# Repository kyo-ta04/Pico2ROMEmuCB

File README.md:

# Pico2ROMEmu - RP2350B Core Board Version
<!--  -->

このプロジェクトは Pico2ROMEmuに RP2350B Core Boardを使用した簡単で高速なROMエミュレータです  
[English Readme](./README.en.md)

## 特徴
- 詳しくは[Pico2ROMEmu](https://github.com/kyo-ta04/Pico2ROMEmuBR)をご覧ください。

## 構成
- KiCad 回路図、PCB、ガーバーファイルはこちら→ [./PCB/](./PCB/) (**2025/11/09 追加 V1.0 R0.1**)
  - KiCad Ver9.0.6、 JLCPCB Fabrication Toolkit Plugin 使用
- `saki80mon041_const.c` などの ROMデータ部分は [https://github.com/yyhayami/saki80mon041](https://github.com/yyhayami/saki80mon041) 由来です。  
UNIMON for SAKI80は、asano氏が公開されているUniversal MonitorをベースにAki.H氏による大幅な拡張がなされてEMUZ80用に公開されているEMUZ80_Monitor Rev.B04を @yyhayami氏が Super AKI-80 で動作するよう移植したものです。
- `rom_basic_const.c` などの ROM-BASIC 部分は [saki80basic](https://github.com/vintagechips/saki80basic) 由来です。
  - 元の[BASICサブセット](http://searle.x10host.com/cpm/index.html)は Grant Searle さんが作成したものであり、[Super AKI-80用に @vintagechip（電脳伝説）](https://vintagechips.wordpress.com/2025/04/24/saki80basic/)さんが移植・改良されています。
- [Tom's SBC](https://oshwlab.com/peabody1929/CPM_Z80_Board_REV_B_copy-76313012f79945d3b8b9d3047368abf7)はpeabody1929さんが作成したものであり、ROMデータは[CP/M machine - Grant Searle](http://searle.x10host.com/cpm/index.html) 由来です。
- [68k-nano](https://github.com/74hc595/68k-nano)は Matt Sarnoff(74hc595)さんが作成、公開されています。 ROMデータはソースから生成しました。
- RP2350 PIO ROMエミュレーション部分は @tendai22plus さんの [ROMエミュレーション](https://github.com/tendai22/emuz80_pico2/blob/main/doc/ROM_EMULATION.md) を参考にさせていただいてます。　参考: [emuz80_pico2](https://github.com/tendai22/emuz80_pico2) 
- 使用している WeAct StudioのRP2350B Core Boardは、Raspberry Pi RP2350Bマイクロコントローラを搭載したコンパクトな開発ボードで、サイズわずか41.4×41.1mmながら全48本のI/Oピンを2つの30ピンヘッダー引き出しています。  
Github : [WeActStudio.RP2350BCoreBoard](https://github.com/WeActStudio/WeActStudio.RP2350BCoreBoard)

## 回路図・資料
- 
上記はピン配置の画像です。
- 
上記は回路図の画像です。
- 
上記は saki80mon041.hex使用時の実行例画像です。
- 
上記は SAKI80MB.HEX使用時の実行例画像です。

## ライセンス
- 本プロジェクトのソースコードは MIT ライセンスです。
- ROMデータ部分などは元サイトおよび改編元のライセンスを参照してください。

## 免責事項
本ソフトウェアは現状のまま提供されます。いかなる損害についても作者は責任を負いません。

## 謝辞
- Grant Searle さん（[BASICサブセット版/CP/M machine 作者）](http://searle.x10host.com/index.html)）
- @vintagechip さん（[電脳伝説さん Super AKI-80用BASIC 作者](https://vintagechips.wordpress.com/)）
- @tendai22plus さん ([emuz80_pico2  作者](https://github.com/tendai22/emuz80_pico2))
- peabody1929 さん ([Tom's SBC 作者](https://oshwlab.com/peabody1929/works))
- Matt Sarnoff(74hc595)さん ([68k-nano 作者](https://github.com/74hc595/68k-nano))
- @yyhayamiさん（[saki80mon041 作者）](https://github.com/yyhayami/saki80mon041)）
- @electrelic(asano)さん（[Universal Monitor 作者）](https://electrelic.com/electrelic/node/1317)）
- @akih_san(Aki.h) さん（[EMUZ80-MON 作者](https://github.com/akih-san/EMUZ80-MON)）
- @shippoiincho さん、 @kondo_pc88 さん、 @TororoLab さん、 @I_HaL さん、 @antarcticlion さん、 @GAPUX さん、 @Tanuki_Bayashin さん、 @applesorce さん、@W88DodPECuThLOl さんを始めとしたアドバイス、イイね、RPしていただいた皆様。
- Raspberry Pi Pico SDK 開発者の皆様
- 本プロジェクトに関わる全ての方々
- [Pico2ROMEmu](https://github.com/kyo-ta04/Pico2ROMEmuBR)もご覧ください。

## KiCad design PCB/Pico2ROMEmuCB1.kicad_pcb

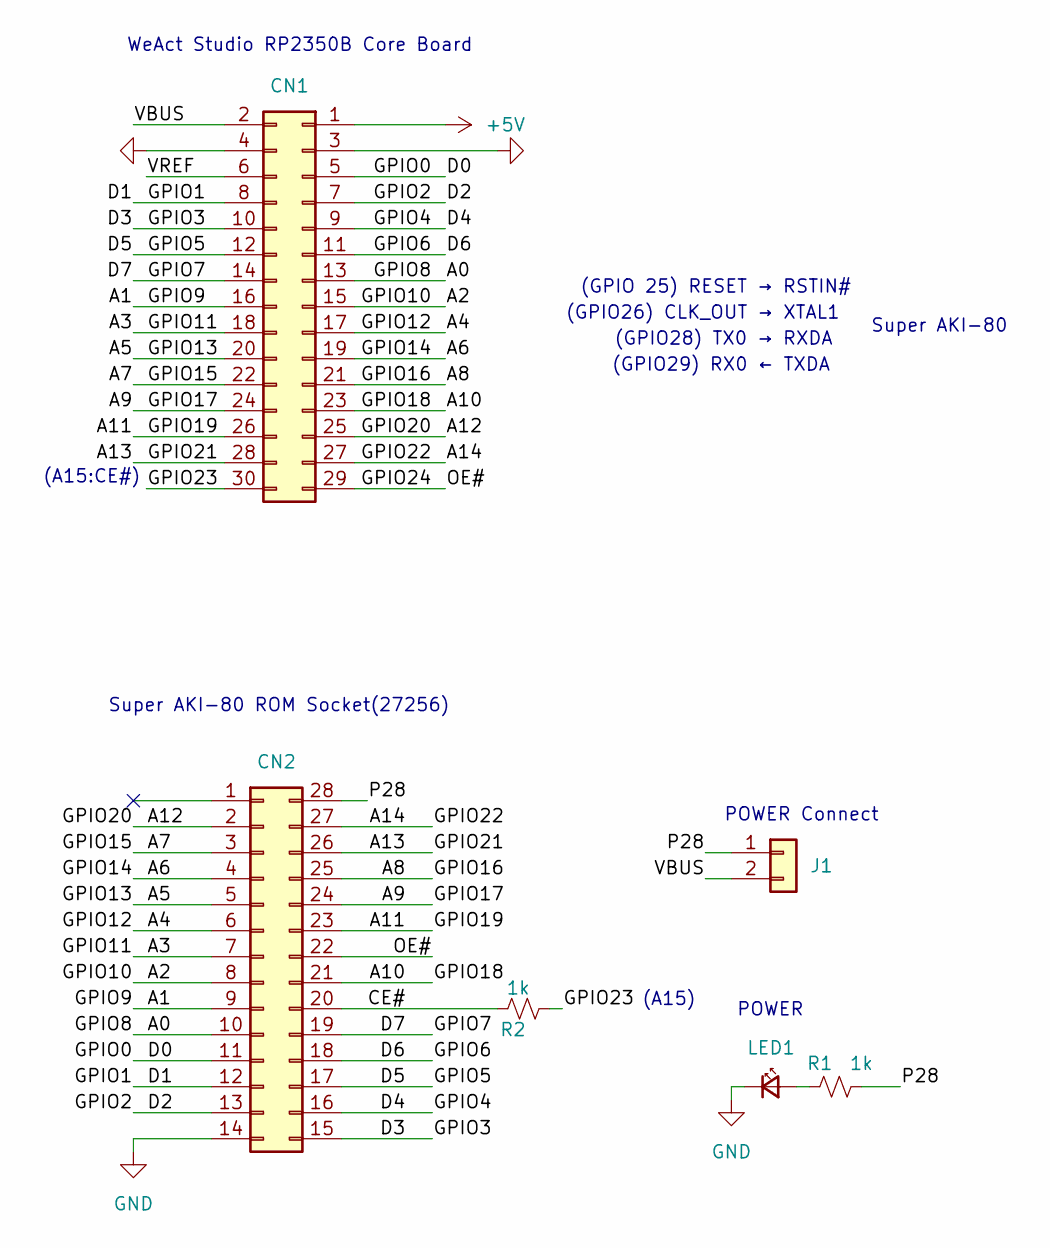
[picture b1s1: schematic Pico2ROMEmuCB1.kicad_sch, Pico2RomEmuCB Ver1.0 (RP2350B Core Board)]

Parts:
CN1: Conn_02x15; PinSocket_2x15_P2.54mm_Horizontal
CN2: Conn_02x14_Counter_Clockwise; DIP-28_W15.24mm_Socket
J1: Conn_01x02; PinHeader_1x02_P2.54mm_Vertical
LED1: LED_Small; LED_D3.0mm
R1, R2: 1k; R_Axial_DIN0204_L3.6mm_D1.6mm_P5.08mm_Horizontal

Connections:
+5V: CN1.1
/A0: CN1.13, CN2.10
/A1: CN1.16, CN2.9
/A2: CN1.15, CN2.8
/A3: CN1.18, CN2.7
/A4: CN1.17, CN2.6
/A5: CN1.20, CN2.5
/A6: CN1.19, CN2.4
/A7: CN1.22, CN2.3
/A8: CN1.21, CN2.25
/A9: CN1.24, CN2.24
/A10: CN1.23, CN2.21
/A11: CN1.26, CN2.23
/A12: CN1.25, CN2.2
/A13: CN1.28, CN2.26
/A14: CN1.27, CN2.27
/CE#: CN2.20, R2.2
/D0: CN1.5, CN2.11
/D1: CN1.8, CN2.12
/D2: CN1.7, CN2.13
/D3: CN1.10, CN2.15
/D4: CN1.9, CN2.16
/D5: CN1.12, CN2.17
/D6: CN1.11, CN2.18
/D7: CN1.14, CN2.19
/GPIO23: CN1.30, R2.1
/GPIO24: CN1.29, CN2.22
/P28: CN2.28, J1.1, R1.1
/VBUS: CN1.2, J1.2
/VREF: CN1.6
GND: CN1.3, CN1.4, CN2.14, LED1.1 (K)
unnamed: LED1.2 (A), R1.2

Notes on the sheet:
POWER Connect
Super AKI-80
(GPIO28) TX0 → RXDA
WeAct Studio RP2350B Core Board
Super AKI-80 ROM Socket(27256)
POWER
(A15:CE#)
(GPIO26) CLK_OUT → XTAL1
(GPIO 25) RESET → RSTIN#
(GPIO29) RX0 ← TXDA
(A15)

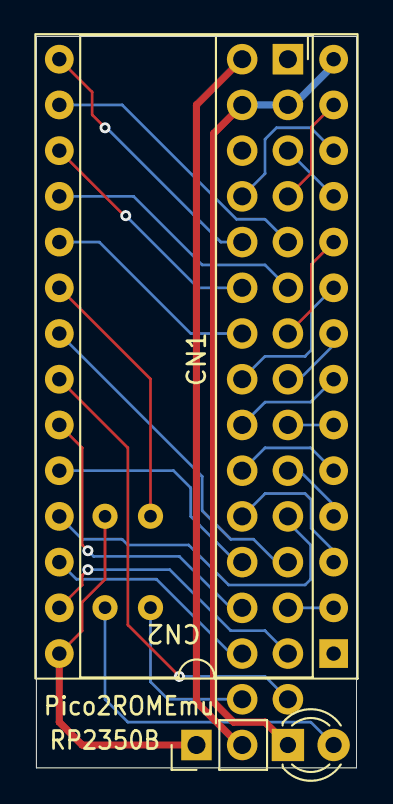
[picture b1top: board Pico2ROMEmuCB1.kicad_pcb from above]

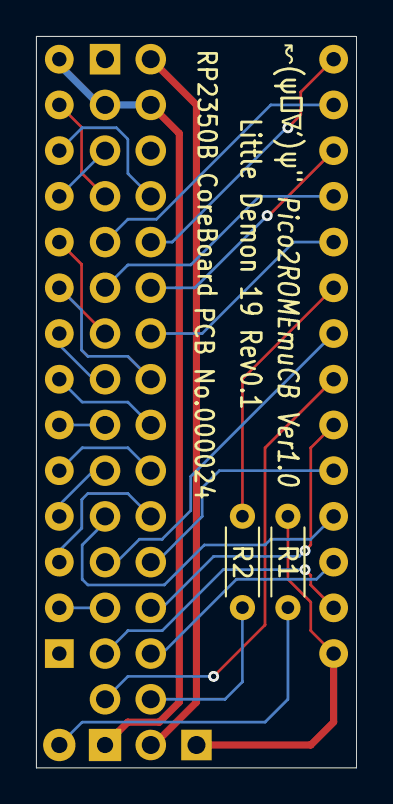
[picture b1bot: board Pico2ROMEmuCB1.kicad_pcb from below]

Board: 2 copper layers, 17.8 x 40.6 mm, 6 parts (2 on the bottom side), 30 nets.

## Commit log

2025-10-04 init
2025-10-04 add image
2025-10-04 add uf2
2025-10-05 回路図の差替え
2025-10-06 開始メッセージ修正
2025-10-06 READMEに実行例追加
2025-10-06 画像差替え
2025-10-13 A13,14追加、コメント修正
2025-10-13 rom_saki80mon041に変更
2025-10-13 README.md修正、画像変更
2025-10-13 README.en.md修正
2025-10-13 README修正
2025-11-02 CB1 PCB
2025-11-03 README,IMG update CB1
2025-11-04 Change RESET to pseudo-open-drain output.
2025-11-04 change image
2025-11-04 modify
2025-11-09 PCB ADD
2025-11-09 png file delete
2025-11-10 uf2 入替え
2025-11-10 回路素 修正
2025-12-20 不要ファイル削除
2026-01-11 コメント修正
2026-01-14 PINOUT追加
